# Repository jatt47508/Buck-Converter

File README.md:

# 12 V → 5 V Buck Converter

A 12 V to 5 V step-down (buck) DC–DC converter designed in **KiCad 10**, simulated in **LTspice**, and presented as an interactive, scroll-driven engineering walkthrough.

**Live site → https://jatt47508.github.io/Buck-Converter/**

## Overview

The converter switches a 12 V input at 100 kHz through a 47 µH inductor and a 220 µF output capacitor, delivering a 5 V-class rail into a 2.5 Ω load. The repository contains the real design sources: the KiCad schematic, a 2-layer PCB, the STEP model, and the LTspice transient deck.

The website takes the board apart in 3D, explains the switching states, plots the simulated waveforms, inspects the PCB layout, and lets you orbit and probe the assembled board in a final interactive lab.

## Simulated results

Measured from the committed LTspice transient run (10 ms, time-weighted):

| Quantity | Value |
| --- | --- |
| Average output | 4.910 V |
| Output ripple | 59.2 mV (1.21 %) |
| Duty cycle | 44.6 % |
| Inductor current | 1.965 A avg, 0.797 A ripple |
| Efficiency | 90.9 % at 2.5 Ω |
| Switching frequency | 100 kHz |

These are **simulation results, not bench measurements**. The ideal duty-cycle figure (41.7 %) and the simulated duty cycle differ because of diode and conduction losses.

## Project status — draft revision

This is an honest draft, not a validated or fabricated design. A design review of the committed PCB found:

- The MOSFET gate pad is marked **no-connect** and has no driver.
- Two MOSFET drain pads have no net assigned.
- The `/Vin` net reaches only the input jack — 12 V does not reach the switch.

There is no DRC report in the repository, and the board has not been manufactured or measured. The website states these findings directly rather than presenting the layout as production-ready.

## What's in the repository

- `12V_to_5V_Buck/` — KiCad project (`.kicad_sch`, `.kicad_pcb`, `.kicad_pro`) and `buck_converter.step`
- `LTspice/` — transient deck, plot settings, and related simulation schematics
- `src/` — the interactive site (React + TypeScript + three.js)
- `public/` — derived 3D models, renders, schematic export, and the waveform CSV

## Site sections

1. **Assembly** — scroll-driven 3D reveal, explode, and annotated assembly
2. **Introduction** — what the board is and what it is not
3. **Working principle** — switching states and the ideal duty-cycle relationship
4. **Circuit** — schematic, component list, nets, and review findings
5. **Simulation** — waveforms, operating point, and an ideal buck calculator
6. **PCB** — real renders, stack-up, dimensions, and layout review
7. **Downloads** — the actual KiCad, STEP, LTspice, and CSV files
8. **PCB Lab** — orbit, explode, and inspect the board interactively

## Built with

React 19 · TypeScript · Vite · three.js / React Three Fiber · KiCad 10 · LTspice
Type: Anton, Archivo, IBM Plex Mono.

## Academic project and disclaimer

© 2026 Jatin Kumar Mallick. Educational use only.

This is a personal passion project built to learn and demonstrate power-electronics design. It is not a commercial product and should not be trusted for industry-grade, production, or safety-critical use. The board has not been fabricated or measured, and all electrical results come from simulation. Simulation data comes from the included LTspice deck; design files come from the included KiCad project. All third-party libraries remain under their respective licenses.

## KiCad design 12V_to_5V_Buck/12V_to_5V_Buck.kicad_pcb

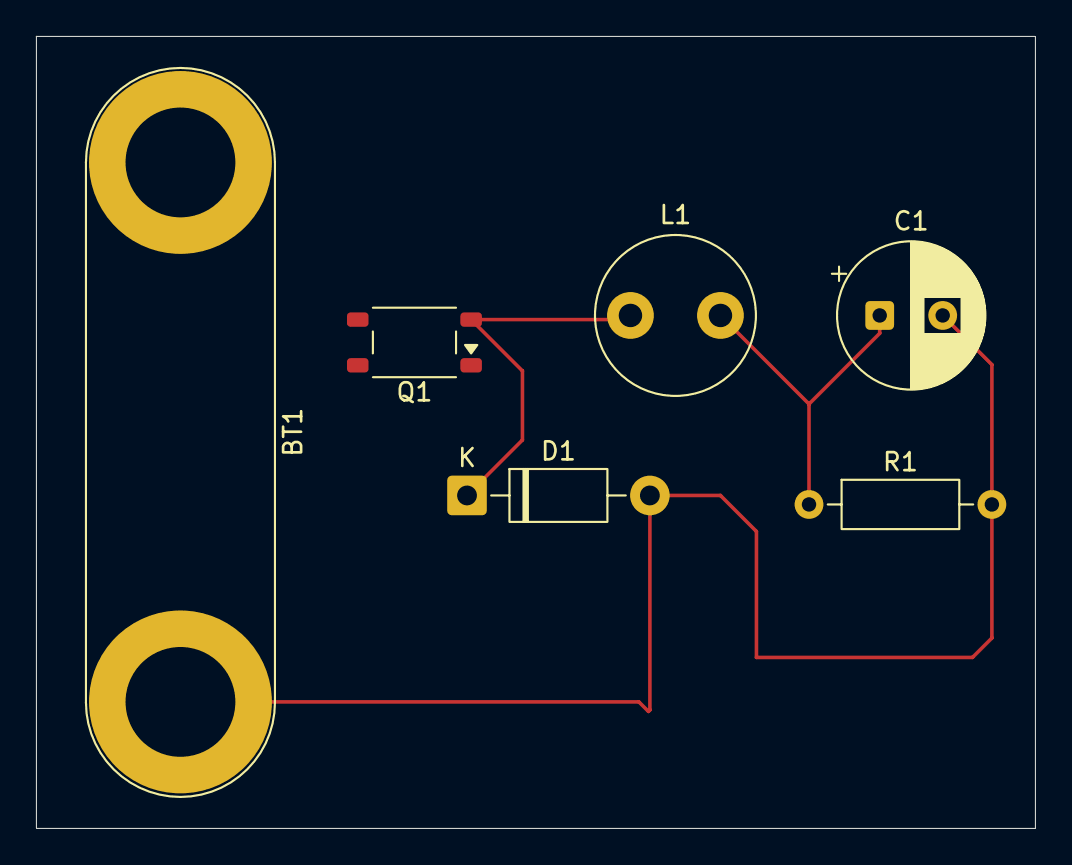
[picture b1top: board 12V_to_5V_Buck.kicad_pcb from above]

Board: 2 copper layers, 55.5 x 44.0 mm, 6 parts (0 on the bottom side), 3 nets.

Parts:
BT1: 12v; Banana_Jack_2Pin
C1: 220u; CP_Radial_D8.0mm_P3.50mm
D1: D_Schottky; D_DO-41_SOD81_P10.16mm_Horizontal
L1: 47u; L_Radial_D8.7mm_P5.00mm_Fastron_07HCP
Q1: Q_NMOS_GDS; Toshiba_SOIC-4-6_4.4x3.6mm_P1.27mm
R1: 2.5; R_Axial_DIN0207_L6.3mm_D2.5mm_P10.16mm_Horizontal

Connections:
/Vout: C1.1, L1.2, R1.1
Earth: BT1.2 (-), C1.2, D1.2 (A), R1.2
unnamed: D1.1 (K), L1.1, Q1.3 (S_3)
